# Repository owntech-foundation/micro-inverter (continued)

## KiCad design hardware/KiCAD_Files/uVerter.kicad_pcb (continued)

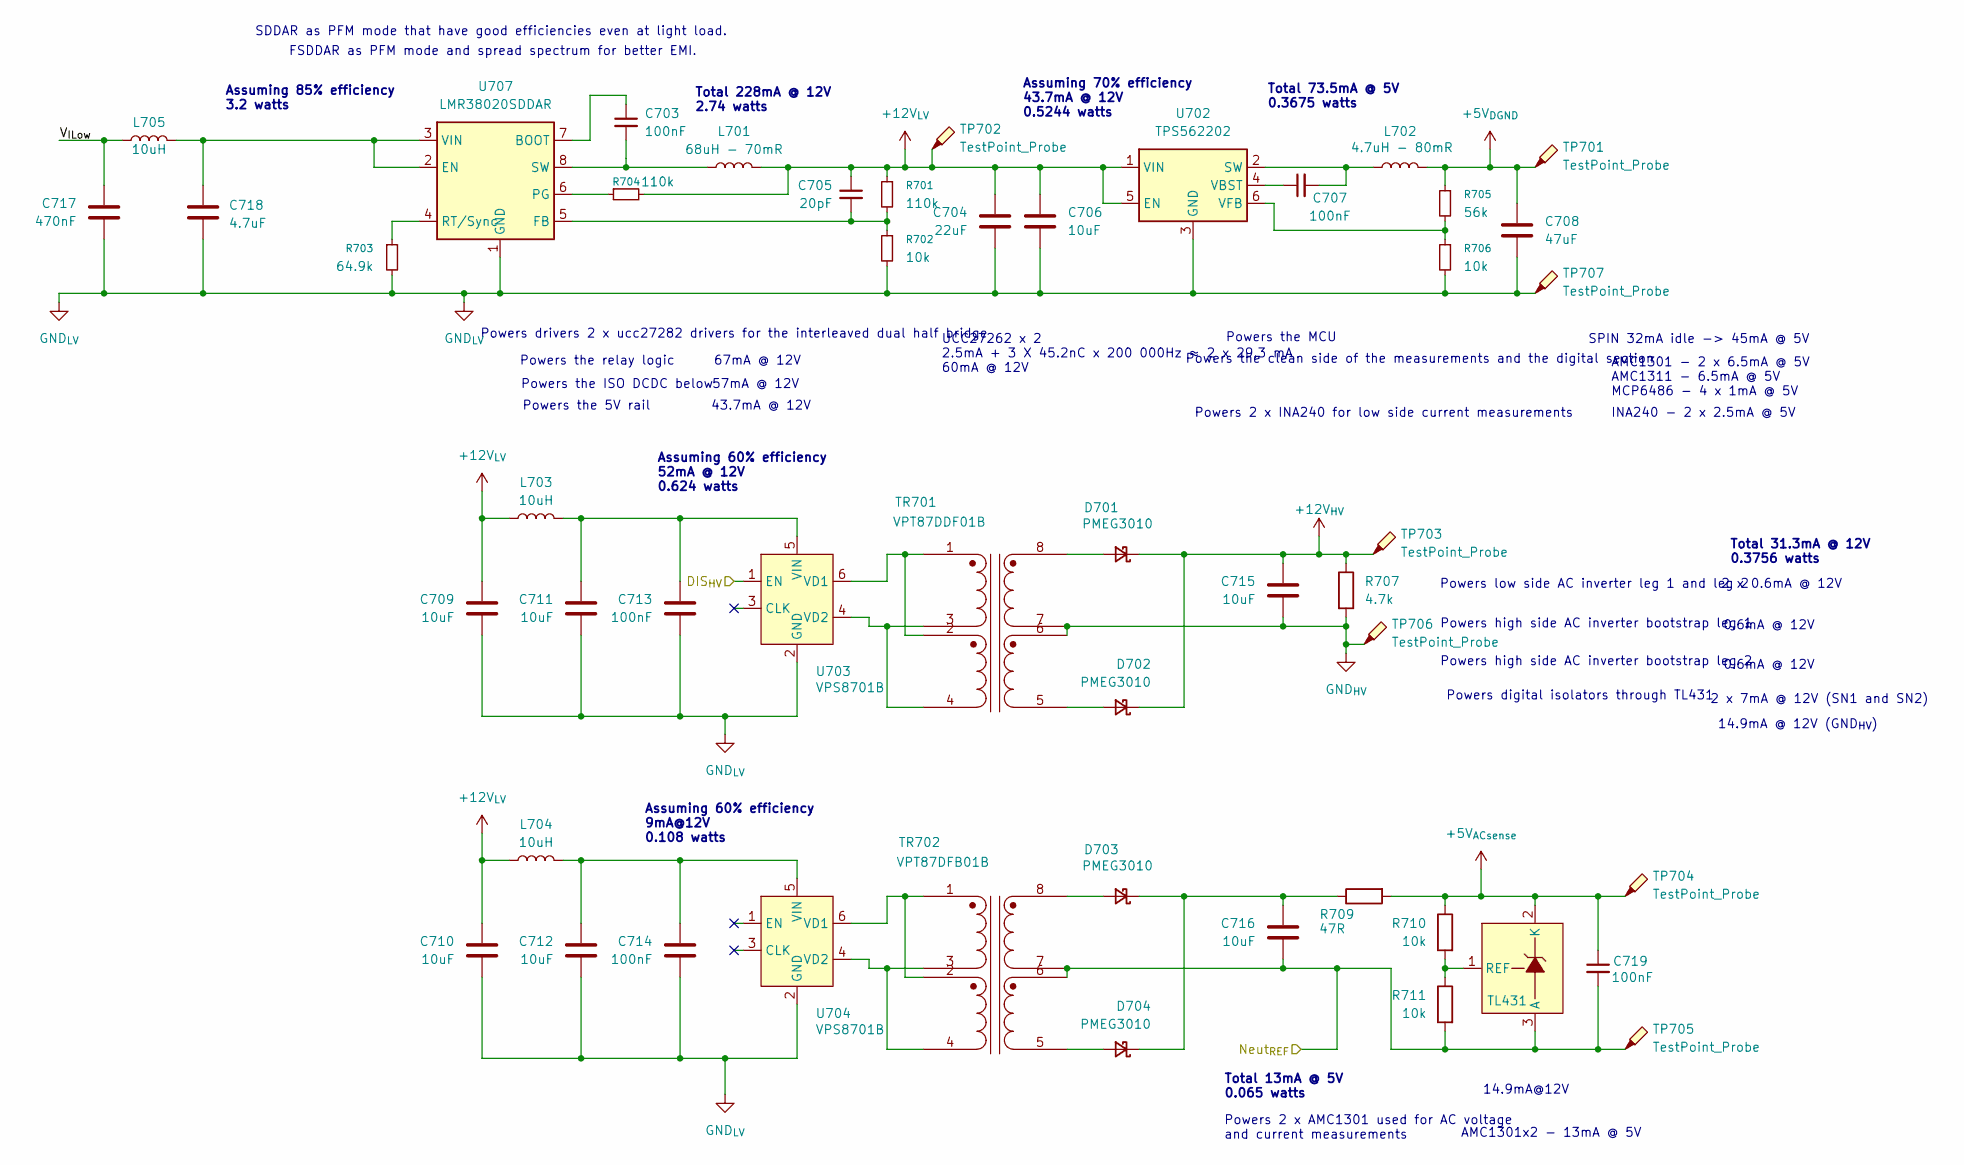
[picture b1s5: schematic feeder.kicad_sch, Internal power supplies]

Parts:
C703, C707, C719: 100nF; C_0805_2012Metric; LCSC C49678
C704: 22uF; C_1210_3225Metric; LCSC C309062
C705: 20pF; C_0805_2012Metric; LCSC C1798
C706, C709, C710, C711, C712, C715, C716: 10uF; C_0805_2012Metric; LCSC C440198
C708: 47uF; C_1206_3216Metric; LCSC C96123
C713, C714: 100nF; C_0603_1608Metric; LCSC C14663
C717: 470nF; C_0805_2012Metric; Voltage_Rating 100V; LCSC C596323
C718: 4.7uF; C_1210_3225Metric; LCSC C381466
D701, D702, D703, D704: PMEG3010; D_SOD-323F; LCSC C2937140
L701: 68uH - 70mR; L_12x12mm_H6mm; LCSC C7587712
L702: 4.7uH - 80mR; L_Cenker_CKCS4020; LCSC C3002596
L703, L704: 10uH; L_0805_2012Metric; LCSC C88173
L705: 10uH; L_1210_3225Metric; LCSC C2047632
R701, R704: 110k; R_0805_2012Metric; LCSC C17422
R702, R706, R710, R711: 10k; R_0805_2012Metric; LCSC C17414
R703: 64.9k; R_0805_2012Metric; LCSC C17788
R705: 56k; R_0805_2012Metric; LCSC C17756
R707: 4.7k; R_0603_1608Metric; LCSC C23162
R709: 47R; R_0805_2012Metric; LCSC C17714
TP701, TP702, TP703, TP704, TP705, TP706, TP707: TestPoint_Probe; TestPoint_Pad_D1.0mm
TR701: VPT87DDF01B; VPT87BB-01B; LCSC C2846916
TR702: VPT87DFB01B; VPT87BB-01B; LCSC C2846915
U702: TPS562202; SOT-563; LCSC C2877547
U703, U704: VPS8701B; SOT-23-6; LCSC C5189123
U705: TL431; SOT-23; LCSC C181103
U707: LMR38020SDDAR; Texas_HSOP-8-1EP_3.9x4.9mm_P1.27mm_ThermalVias; LCSC C3192337

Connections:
+5V_{ACsense}: C719.1, R709.2, R710.1, TP704.1, U705.2 (K); also elsewhere on the board
+5V_{DGND}: C708.1, L702.2, R705.1, TP701.1; also elsewhere on the board
+12V_{HV}: C715.1, D701.1 (K), D702.1 (K), R707.1, TP703.1; also elsewhere on the board
/Internal power supplies/DIS_{HV}: U703.1 (EN); also elsewhere on the board
/Internal power supplies/Neut_{REF}: C716.2, C719.2, R711.2, TP705.1, TR702.6 (SB), TR702.7 (SA), U705.3 (A); also elsewhere on the board
/Internal power supplies/V_{ILow}: C717.1, L705.1
GND_{HV}: C715.2, R707.2, TP706.1, TR701.6 (SB), TR701.7 (SA); also elsewhere on the board
unnamed: D701.2 (A), TR701.8 (SB)
unnamed: D702.2 (A), TR701.5 (SA)
unnamed: D703.2 (A), TR702.8 (SB)
unnamed: C716.1, D703.1 (K), D704.1 (K), R709.1
unnamed: D704.2 (A), TR702.5 (SA)
unnamed: C707.2, L702.1, U702.2 (SW)
unnamed: C707.1, U702.4 (VBST)
unnamed: R705.2, R706.1, U702.6 (VFB)
unnamed: TR701.1 (AA), TR701.2 (AA), U703.6 (VD1)
unnamed: TR701.3 (AB), TR701.4 (AB), U703.4 (VD2)
unnamed: C711.1, C713.1, L703.2, U703.5 (VIN)
unnamed: TR702.1 (AA), TR702.2 (AA), U704.6 (VD1)
unnamed: TR702.3 (AB), TR702.4 (AB), U704.4 (VD2)
unnamed: C712.1, C714.1, L704.2, U704.5 (VIN)
unnamed: R710.2, R711.1, U705.1 (REF)
unnamed: C703.1, U707.7 (BOOT)
unnamed: C718.1, L705.2, U707.2 (EN), U707.3 (VIN)
unnamed: C705.2, R701.2, R702.1, U707.5 (FB)
unnamed: R704.1, U707.6 (PG)
unnamed: R703.1, U707.4 (RT/Sync)
unnamed: C703.2, L701.1, U707.8 (SW)

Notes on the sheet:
Powers the 5V rail
Powers digital isolators through TL431
Total 73.5mA @ 5V 0.3675 watts
Assuming 70% efficiency 43.7mA @ 12V 0.5244 watts
AMC1301x2 - 13mA @ 5V
INA240 - 2 x 2.5mA @ 5V
Powers the clean side of the measurements and the digital section
Powers 2 x AMC1301 used for AC voltage and current measurements
Powers high side AC inverter bootstrap leg 1
Total 13mA @ 5V 0.065 watts
Assuming 60% efficiency 9mA@12V 0.108 watts
Assuming 60% efficiency 52mA @ 12V 0.624 watts
0.6mA @ 12V
Powers 2 x INA240 for low side current measurements
Powers low side AC inverter leg 1 and leg 2
Powers the ISO DCDC below
SPIN 32mA idle -> 45mA @ 5V
14.9mA @ 12V (GND_{HV})
Powers drivers 2 x ucc27282 drivers for the interleaved dual half bridge
57mA @ 12V
UCC27262 x 2 2.5mA + 3 X 45.2nC x 200 000Hz ≈ 2 x 29.3 mA 60mA @ 12V
FSDDAR as PFM mode and spread spectrum for better EMI.
43.7mA @ 12V
2 x 0.6mA @ 12V
AMC1301 - 2 x 6.5mA @ 5V AMC1311 - 6.5mA @ 5V MCP6486 - 4 x 1mA @ 5V
14.9mA@12V
2 x 7mA @ 12V (SN1 and SN2)
Total 228mA @ 12V 2.74 watts
Powers the MCU
Assuming 85% efficiency 3.2 watts
Total 31.3mA @ 12V 0.3756 watts
Powers the relay logic
67mA @ 12V
Powers high side AC inverter bootstrap leg 2
SDDAR as PFM mode that have good efficiencies even at light load.

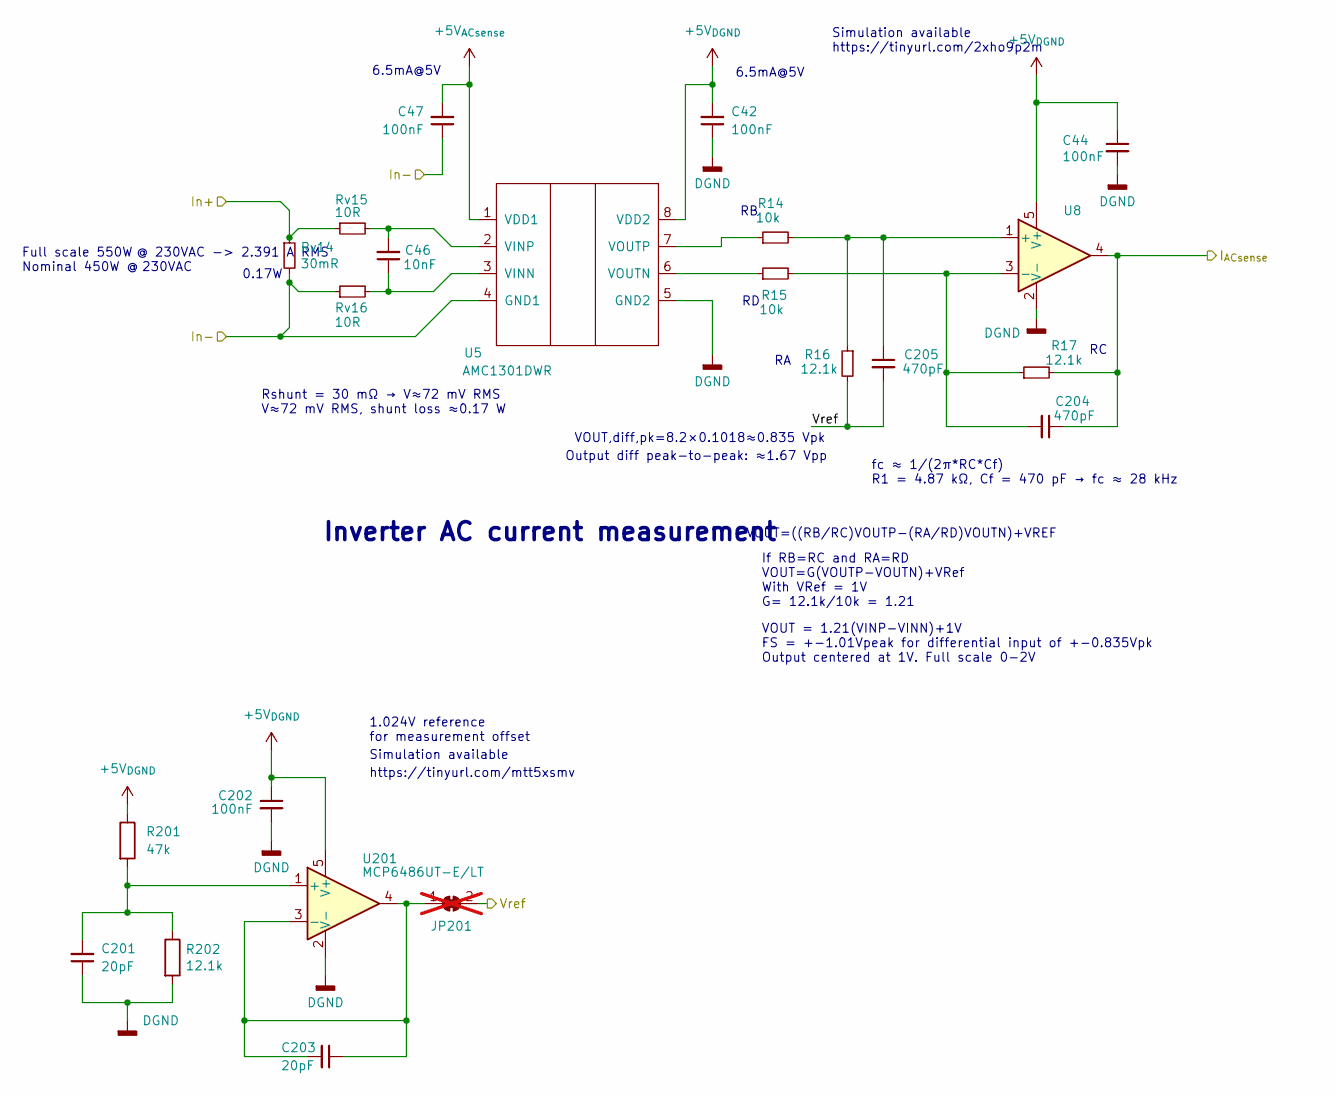
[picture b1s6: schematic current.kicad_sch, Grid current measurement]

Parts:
C42, C47: 100nF; C_1206_3216Metric; LCSC C24497
C44: 100nF; C_0805_2012Metric; LCSC C49678
C46: 10nF; C_0805_2012Metric; LCSC C1710
C201, C203: 20pF; C_0805_2012Metric; LCSC C1798
C202: 100nF; C_0805_2012Metric; Voltage_Rating 50V; LCSC C49678
C204, C205: 470pF; C_0805_2012Metric; LCSC C1743
JP201: SolderJumper; SolderJumper-2_P1.3mm_Bridged_RoundedPad1.0x1.5mm; not fitted
R14, R15: 10k; R_0805_2012Metric; LCSC C17414
R16, R17, R202: 12.1k; R_0805_2012Metric; LCSC C17431
R201: 47k; R_0805_2012Metric; LCSC C17713
Rv14: 30mR; R_2512_6332Metric; LCSC C46634451
Rv15, Rv16: 10R; R_0805_2012Metric; LCSC C17415
U5: AMC1301DWR; SOIC-8_7.5x5.85mm_P1.27mm; LCSC C190273
U8, U201: MCP6486UT-E/LT; SOT-353_SC-70-5; LCSC C5224800

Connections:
+5V_{ACsense}: C47.2, U5.1 (VDD1); also elsewhere on the board
+5V_{DGND}: C42.2, C44.1, C202.1, R201.1, U5.8 (VDD2), U8.5 (V+), U201.5 (V+); also elsewhere on the board
/Internal power supplies/Neut_{REF}: C47.1, Rv14.2, Rv16.1, U5.4 (GND1); also elsewhere on the board
/Microcontroller/I_{AC}: C204.1, R17.2, U8.4; also elsewhere on the board
/Power stage/AC Current sense/In+: Rv14.1, Rv15.1; also elsewhere on the board
/Power stage/AC Current sense/Vref: C205.2, JP201.2 (B), R16.2; also elsewhere on the board
unnamed: C203.1, C203.2, JP201.1 (A), U201.3 (-), U201.4
unnamed: C46.1, Rv16.2, U5.3 (VINN)
unnamed: C46.2, Rv15.2, U5.2 (VINP)
unnamed: R15.1, U5.6 (VOUTN)
unnamed: R14.1, U5.7 (VOUTP)
unnamed: C205.1, R14.2, R16.1, U8.1 (+)
unnamed: C204.2, R15.2, R17.1, U8.3 (-)
unnamed: C201.2, R201.2, R202.1, U201.1 (+)

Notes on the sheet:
https://tinyurl.com/mtt5xsmv
Simulation available https://tinyurl.com/2xho9p2m
fc ​≈ 1/(2π*RC*Cf)​ R1 = 4.87 kΩ, Cf = 470 pF → fc ≈ 28 kHz
VOUT​=((RB/RC)VOUTP​−(RA/RD)VOUTN​)+VREF​
6.5mA@5V
0.17W
Simulation available
VOUT = 1.21(VINP-VINN)+1V FS = +-1.01Vpeak for differential input of +-0.835Vpk Output centered at 1V. Full scale 0-2V
Output diff peak-to-peak: ≈1.67 Vpp
1.024V reference for measurement offset
Inverter AC current measurement
Rshunt = 30 mΩ → V≈72 mV RMS V≈72 mV RMS, shunt loss ≈0.17 W
If RB=RC and RA=RD VOUT​=G(VOUTP​−VOUTN​)+VRef With VRef = 1V G= 12.1k/10k = 1.21
VOUT,diff,pk​=8.2×0.1018≈0.835 Vpk
Full scale 550W @ 230VAC -> 2.391 A RMS Nominal 450W @ 230VAC

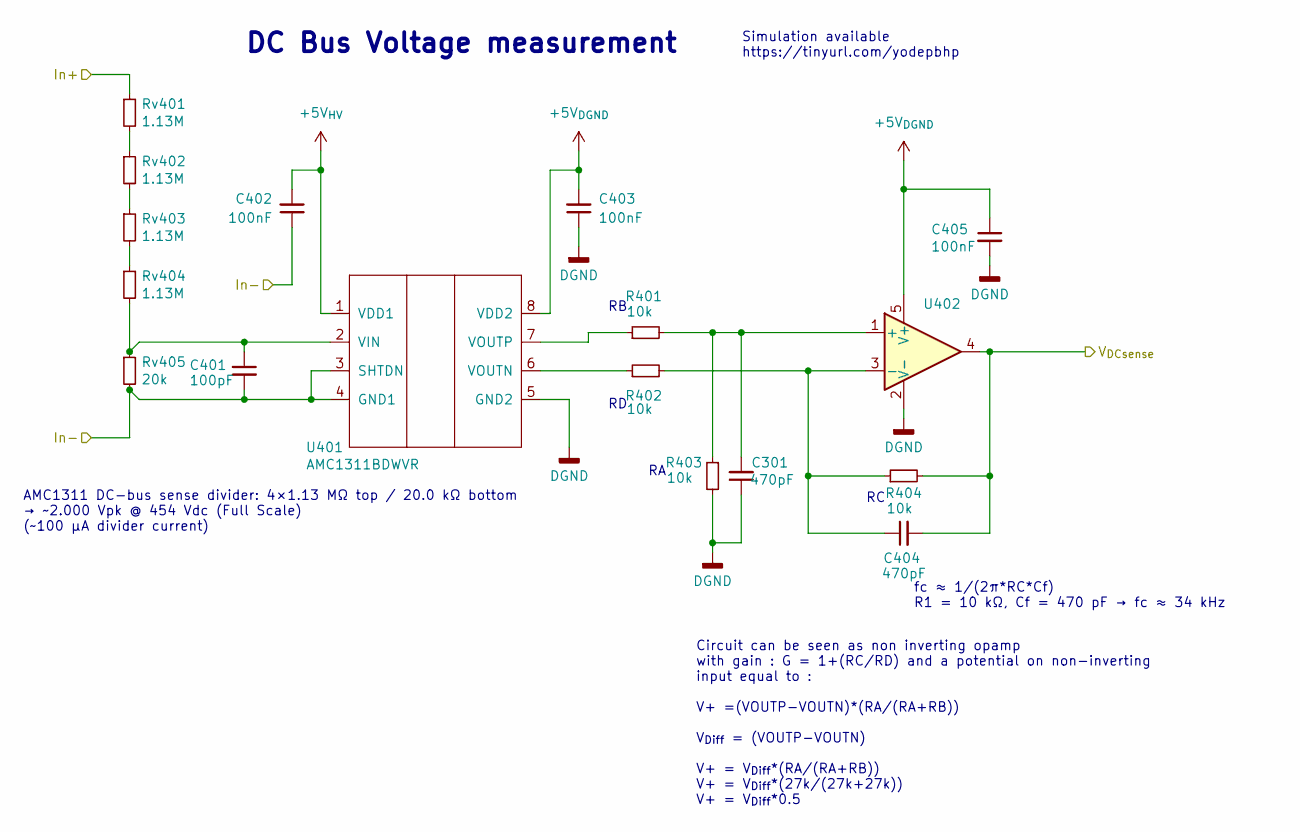
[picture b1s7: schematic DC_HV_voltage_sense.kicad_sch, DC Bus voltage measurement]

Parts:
C301, C404: 470pF; C_0805_2012Metric; LCSC C1743
C401: 100pF; C_0805_2012Metric; LCSC C1790
C402, C403: 100nF; C_1206_3216Metric; LCSC C24497
C405: 100nF; C_0805_2012Metric; LCSC C49678
R401, R402, R403, R404: 10k; R_0805_2012Metric; LCSC C17414
Rv401, Rv402, Rv403, Rv404: 1.13M; R_0805_2012Metric; LCSC C2091141
Rv405: 20k; R_0805_2012Metric; LCSC C4328
U401: AMC1311BDWVR; SOIC-8_7.5x5.85mm_P1.27mm; LCSC C783598
U402: MCP6486UT-E/LT; SOT-353_SC-70-5; LCSC C5224800

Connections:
+5V_{DGND}: C403.2, C405.1, U401.8 (VDD2), U402.5 (V+); also elsewhere on the board
+5V_{HV}: C402.2, U401.1 (VDD1); also elsewhere on the board
/Microcontroller/V_{DCBus}: C404.2, R404.2, U402.4; also elsewhere on the board
/Power stage/HV_{BUS}: Rv401.1; also elsewhere on the board
GND_{HV}: C401.2, C402.1, Rv405.2, U401.3 (SHTDN), U401.4 (GND1); also elsewhere on the board
unnamed: Rv401.2, Rv402.1
unnamed: Rv402.2, Rv403.1
unnamed: Rv403.2, Rv404.1
unnamed: C401.1, Rv404.2, Rv405.1, U401.2 (VIN)
unnamed: R402.1, U401.6 (VOUTN)
unnamed: R401.1, U401.7 (VOUTP)
unnamed: C301.2, R401.2, R403.1, U402.1 (+)
unnamed: C404.1, R402.2, R404.1, U402.3 (-)

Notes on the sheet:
AMC1311 DC-bus sense divider: 4×1.13 MΩ top / 20.0 kΩ bottom → ~2.000 Vpk @ 454 Vdc (Full Scale) (~100 µA divider current)
Circuit can be seen as non inverting opamp with gain : G = 1+(RC/RD) and a potential on non-inverting input equal to : V+ =(VOUTP-VOUTN)*(RA/(RA+RB)) V_{Diff} = (VOUTP-VOUTN) V+ = V_{Diff}*(RA/(RA+RB)) V+ = V_{Diff}*(27k/(27k+27k)) V+ = V_{Diff}*0.5
DC Bus Voltage measurement
fc ​≈ 1/(2π*RC*Cf)​ R1 = 10 kΩ, Cf = 470 pF → fc ≈ 34 kHz
Simulation available https://tinyurl.com/yodepbhp

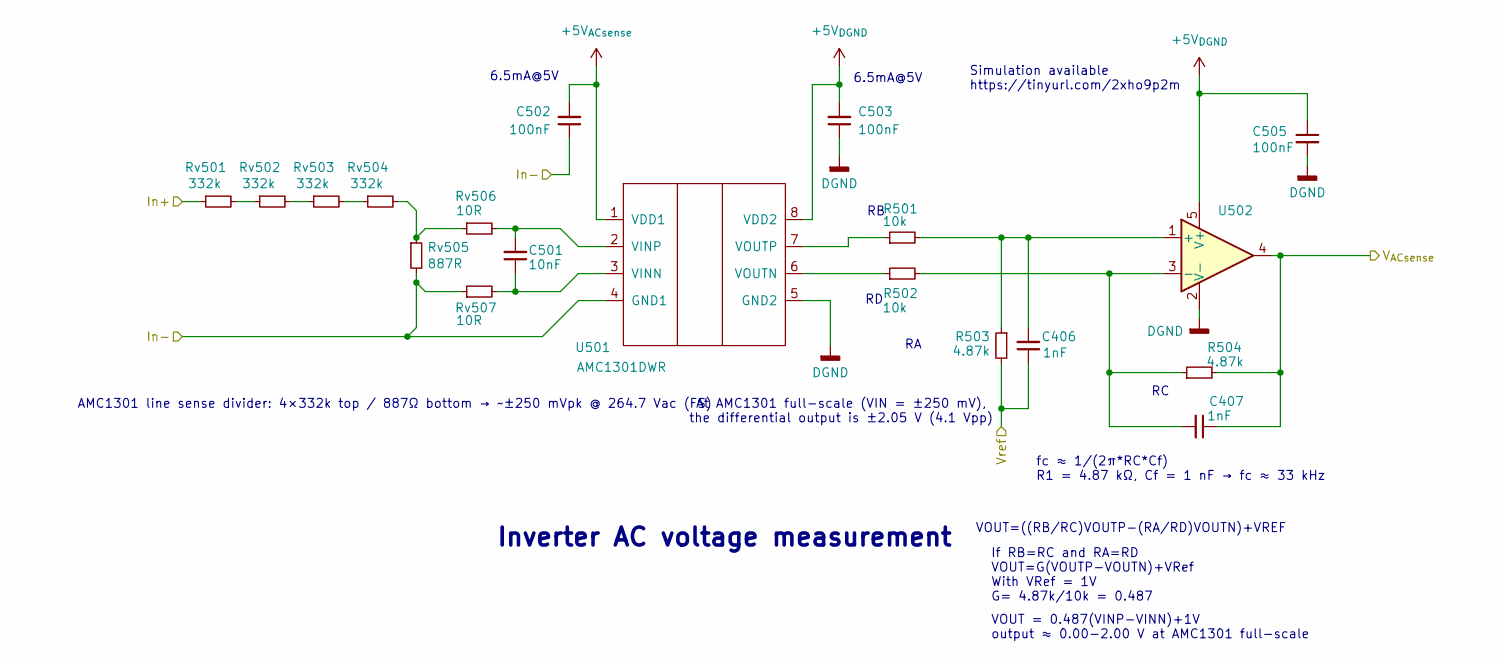
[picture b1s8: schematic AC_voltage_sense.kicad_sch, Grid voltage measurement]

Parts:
C406, C407: 1nF; C_0805_2012Metric; LCSC C46653
C501: 10nF; C_0805_2012Metric; LCSC C1710
C502, C503: 100nF; C_1206_3216Metric; LCSC C24497
C505: 100nF; C_0805_2012Metric; LCSC C49678
R501, R502: 10k; R_0805_2012Metric; LCSC C17414
R503, R504: 4.87k; R_0805_2012Metric; LCSC C228870
Rv501, Rv502, Rv503, Rv504: 332k; R_0805_2012Metric; LCSC C5713304
Rv505: 887R; R_0805_2012Metric; LCSC C144545
Rv506, Rv507: 10R; R_0805_2012Metric; LCSC C17415
U501: AMC1301DWR; SOIC-8_7.5x5.85mm_P1.27mm; LCSC C190273
U502: MCP6486UT-E/LT; SOT-353_SC-70-5; LCSC C5224800

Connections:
+5V_{ACsense}: C502.2, U501.1 (VDD1); also elsewhere on the board
+5V_{DGND}: C503.2, C505.1, U501.8 (VDD2), U502.5 (V+); also elsewhere on the board
/Internal power supplies/Neut_{REF}: C502.1, Rv505.2, Rv507.1, U501.4 (GND1); also elsewhere on the board
/Microcontroller/V_{AC}: C407.1, R504.2, U502.4; also elsewhere on the board
/Power stage/AC Current sense/Vref: C406.1, R503.2; also elsewhere on the board
/Power stage/Grid Voltage sense/In+: Rv501.1; also elsewhere on the board
unnamed: Rv501.2, Rv502.1
unnamed: Rv502.2, Rv503.1
unnamed: Rv503.2, Rv504.1
unnamed: Rv504.2, Rv505.1, Rv506.1
unnamed: C501.1, Rv507.2, U501.3 (VINN)
unnamed: C501.2, Rv506.2, U501.2 (VINP)
unnamed: R502.1, U501.6 (VOUTN)
unnamed: R501.1, U501.7 (VOUTP)
unnamed: C406.2, R501.2, R503.1, U502.1 (+)
unnamed: C407.2, R502.2, R504.1, U502.3 (-)

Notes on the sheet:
VOUT = 0.487(VINP-VINN)+1V output ≈ 0.00-2.00 V at AMC1301 full-scale
Inverter AC voltage measurement
If RB=RC and RA=RD VOUT​=G(VOUTP​−VOUTN​)+VRef With VRef = 1V G= 4.87k/10k = 0.487
6.5mA@5V
At AMC1301 full-scale (VIN = ±250 mV), the differential output is ±2.05 V (4.1 Vpp)
fc ​≈ 1/(2π*RC*Cf)​ R1 = 4.87 kΩ, Cf = 1 nF → fc ≈ 33 kHz
AMC1301 line sense divider: 4×332k top / 887Ω bottom → ~±250 mVpk @ 264.7 Vac (FS)
Simulation available https://tinyurl.com/2xho9p2m
VOUT​=((RB/RC)VOUTP​−(RA/RD)VOUTN​)+VREF​

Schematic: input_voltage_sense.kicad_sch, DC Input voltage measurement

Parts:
C701: 1nF; C_0805_2012Metric; LCSC C46653
C702: 100nF; C_0805_2012Metric; LCSC C49678
Rv701: 1M; R_0805_2012Metric; LCSC C17514
Rv702: 25.6K; R_0805_2012Metric; LCSC C46670
U701: MCP6486UT-E/LT; SOT-353_SC-70-5; LCSC C5224800

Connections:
+5V_{DGND}: C702.1, U701.5 (V+); also elsewhere on the board
/Microcontroller/V_{ILow}: U701.3 (-), U701.4; also elsewhere on the board
/Power stage/V_{ILow}: Rv701.1; also elsewhere on the board
unnamed: C701.1, Rv701.2, Rv702.1, U701.1 (+)

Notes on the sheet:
Filter cutoff ≈ 6.4 kHz
DC input voltage measurement
Full-scale (for 2 V output): ~80 V input

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
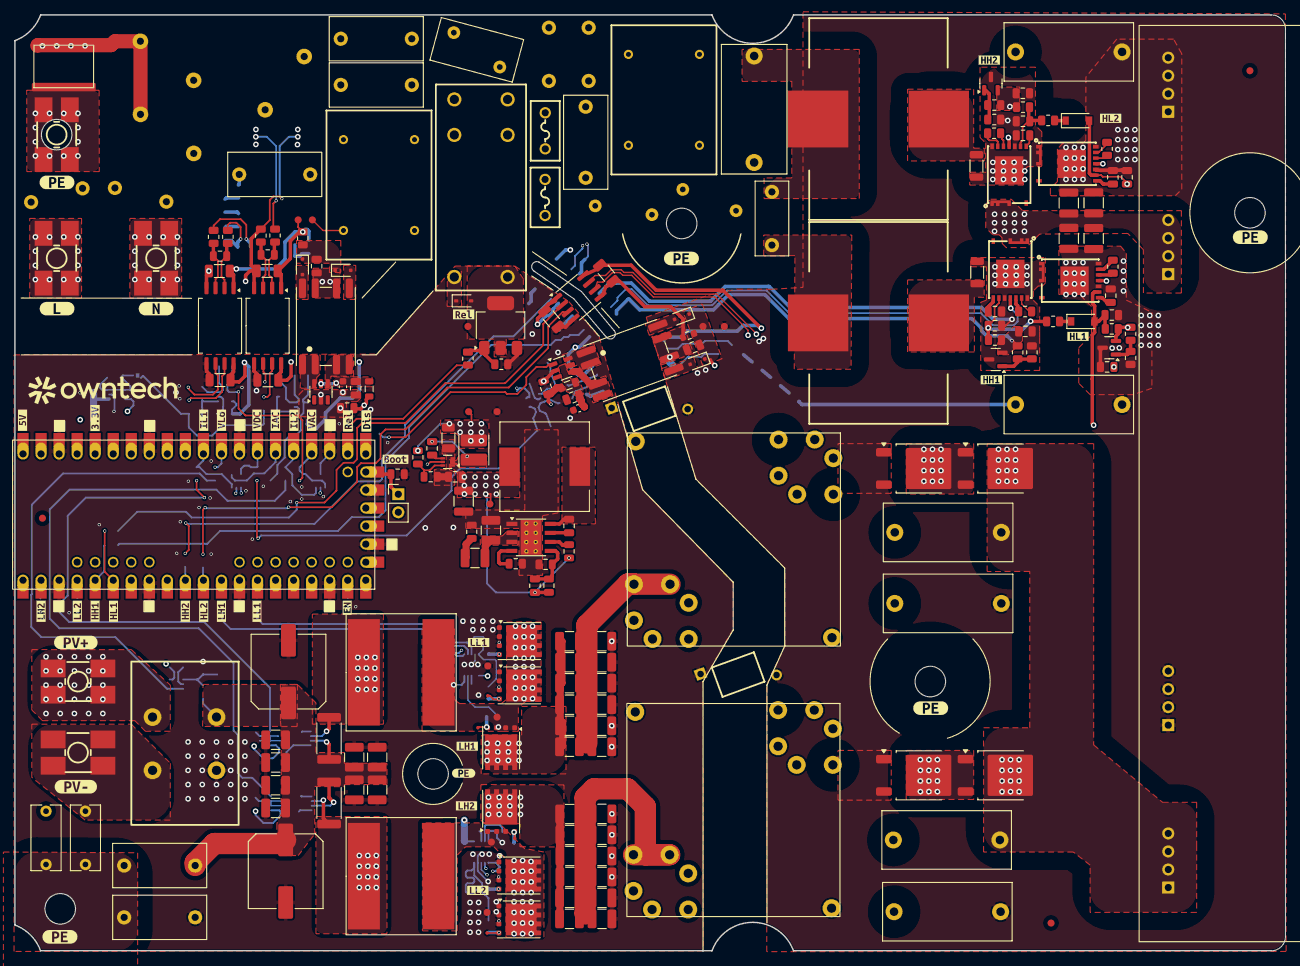
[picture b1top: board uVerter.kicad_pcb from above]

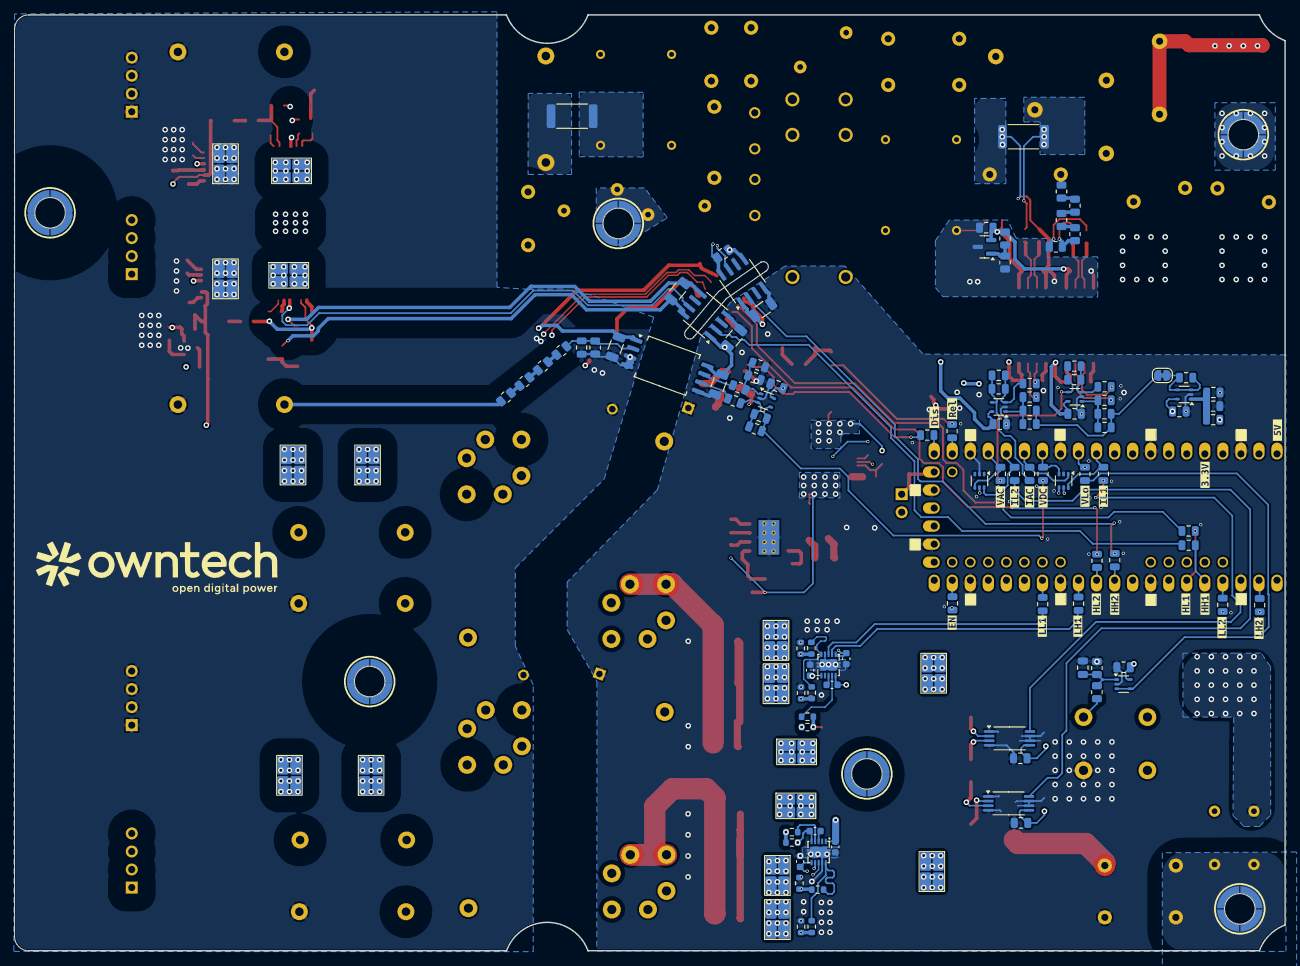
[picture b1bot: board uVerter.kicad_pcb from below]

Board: 4 copper layers, 178.9 x 131.8 mm, 402 parts (147 on the bottom side), 166 nets.

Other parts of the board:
kibuzzard-696E53B6: G***; kibuzzard-696E53B6
kibuzzard-696E53C3, kibuzzard-696E53C3#2, kibuzzard-696E53C3#3, kibuzzard-696E53C3#4, kibuzzard-696E53C3#5: G***; kibuzzard-696E53C3
kibuzzard-696E53FC: G***; kibuzzard-696E53FC
kibuzzard-696E540C: G***; kibuzzard-696E540C
kibuzzard-696E5393: G***; kibuzzard-696E5393
kibuzzard-696EA6EB: G***; kibuzzard-696EA6EB
kibuzzard-6973CF9D, kibuzzard-6973CF9D#2: G***; kibuzzard-6973CF9D
kibuzzard-6973CF69, kibuzzard-6973CF69#2: G***; kibuzzard-6973CF69
kibuzzard-6973CFAE, kibuzzard-6973CFAE#2: G***; kibuzzard-6973CFAE
kibuzzard-6973CFBE, kibuzzard-6973CFBE#2: G***; kibuzzard-6973CFBE
kibuzzard-6973CFD0, kibuzzard-6973CFD0#2: G***; kibuzzard-6973CFD0
kibuzzard-6973CFDB, kibuzzard-6973CFDB#2: G***; kibuzzard-6973CFDB
kibuzzard-6973D0B4, kibuzzard-6973D0B4#2: G***; kibuzzard-6973D0B4
kibuzzard-6973D0CE, kibuzzard-6973D0CE#2: G***; kibuzzard-6973D0CE
kibuzzard-6973D0DA, kibuzzard-6973D0DA#2, kibuzzard-6973D0DA#3: G***; kibuzzard-6973D0DA
kibuzzard-6973D0E6, kibuzzard-6973D0E6#2: G***; kibuzzard-6973D0E6
kibuzzard-6973D0F4, kibuzzard-6973D0F4#2: G***; kibuzzard-6973D0F4
kibuzzard-6973D01A, kibuzzard-6973D01A#2: G***; kibuzzard-6973D01A
kibuzzard-6973D1AD, kibuzzard-6973D1AD#2: G***; kibuzzard-6973D1AD
kibuzzard-6973D002, kibuzzard-6973D002#2, kibuzzard-6973D002#3: G***; kibuzzard-6973D002
kibuzzard-6973D2A9: G***; kibuzzard-6973D2A9
kibuzzard-6973D02F: G***; kibuzzard-6973D02F
kibuzzard-6973D09F, kibuzzard-6973D09F#2: G***; kibuzzard-6973D09F
kibuzzard-6973D10C, kibuzzard-6973D10C#2: G***; kibuzzard-6973D10C
kibuzzard-6973D19D, kibuzzard-6973D19D#2: G***; kibuzzard-6973D19D
kibuzzard-6973D24A: G***; kibuzzard-6973D24A
kibuzzard-6973D25B: G***; kibuzzard-6973D25B
kibuzzard-6973D27C: G***; kibuzzard-6973D27C
kibuzzard-6973D28C: G***; kibuzzard-6973D28C
kibuzzard-6973D075, kibuzzard-6973D075#2: G***; kibuzzard-6973D075
kibuzzard-6973D084, kibuzzard-6973D084#2: G***; kibuzzard-6973D084
kibuzzard-6973D253: G***; kibuzzard-6973D253
kibuzzard-6973D261: G***; kibuzzard-6973D261

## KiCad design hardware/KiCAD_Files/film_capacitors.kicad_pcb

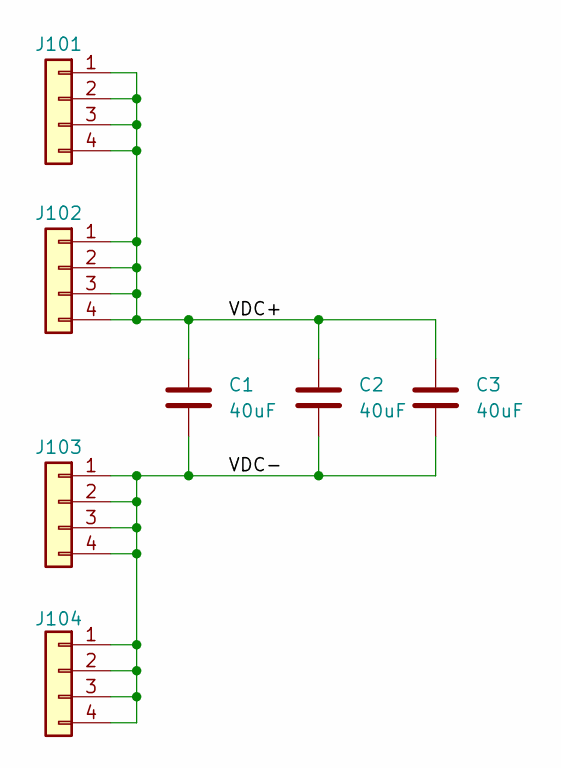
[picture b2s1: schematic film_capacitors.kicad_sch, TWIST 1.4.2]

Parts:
C1, C2, C3: 40uF; 40uF_film; LCSC C52120702
J101, J102, J103, J104: Conn_01x04; PinHeader_1x04_P2.54mm_Horizontal; LCSC C492412

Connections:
/VDC+: C1.1, C2.1, C3.1, J101.1, J101.2, J101.3, J101.4, J102.1, J102.2, J102.3, J102.4
/VDC-: C1.2, C2.2, C3.2, J103.1, J103.2, J103.3, J103.4, J104.1, J104.2, J104.3, J104.4

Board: 2 copper layers, 18 parts (6 on the bottom side), 2 nets, no tracks yet.

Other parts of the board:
kibuzzard-696561C2: G***; kibuzzard-696561C2
kibuzzard-6965612A: G***; kibuzzard-6965612A
kibuzzard-6965618E, kibuzzard-6965618E#2: G***; kibuzzard-6965618E
kibuzzard-69656115: G***; kibuzzard-69656115
kibuzzard-69656160, kibuzzard-69656160#2: G***; kibuzzard-69656160
kibuzzard-69656174, kibuzzard-69656174#2: G***; kibuzzard-69656174
kibuzzard-69656181, kibuzzard-69656181#2: G***; kibuzzard-69656181

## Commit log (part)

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2024-06-20 Initial commit Dual Active Bridge.
2025-07-11 Initial commit micro-inverter
2025-07-11 Spawning a README.md
2025-07-11 Change the repo structure to match standard tree.
2026-03-20 reorganization of the folder
2026-04-09 moved the files around to create a specific hardware testing folder
2026-04-09 added simulations to the hardware folder
2026-04-09 docs(test-plan): align introduction and add system-under-test placeholders
2026-04-09 docs(test-plan): restructure tests 0-3 for safe bring-up progression
2026-04-09 docs(test-plan): reorganize tests 4-5 around control-path and sensing validation
2026-04-09 docs(test-plan): rewrite tests 6-8 as staged power-stage integration
2026-04-09 docs(test-plan): tighten wording and normalize safety formatting
2026-04-09 Small cosmetic changes on the test plan
2026-04-09 updated the images of the system overview
2026-04-10 added a table of contents and a flow chart of the progress
2026-04-10 updates the system overview to better describe the system itself
2026-04-10 updates on the test plan and improvement of the test plan 5
2026-04-10 updates to the tests 5 and 6
2026-04-15 Update to test 7
2026-04-15 updates for test 8
2026-05-18 Adding a LTSpice simulation for the DCDC current fed half bridge.
2026-05-18 Adding a LTSpice simulation for the DCDC current fed half bridge. (#42)
2026-05-20 Added Surge Protection markdown document (#41)
    * Added Surge Protection design note in markdown
    * Added markdown images
    * fixed images path
